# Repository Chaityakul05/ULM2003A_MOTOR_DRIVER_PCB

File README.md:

## ULN2003A Test with ESP and Stepper Motor

This project demonstrates how to drive a 28BYJ-48 stepper motor using the ULN2003A Darlington transistor array with an ESP32 or ESP8266. The ULN2003A is used as a current amplifier and switch to control the stepper motor, which requires more current than the ESP GPIO pins can provide directly. The setup connects the ESP to the four input pins (IN1–IN4) of the ULN2003A, which in turn controls the stepper motor connected to the output pins (OUT1–OUT4). This project helps in understanding how to interface stepper motors with microcontrollers through a driver IC and provides basic motion control using the Arduino Stepper library.

---

##  Example Code (Arduino IDE)

```cpp
#include <Stepper.h>

const int stepsPerRevolution = 2048; // Number of steps per full revolution

// ULN2003 Motor Driver Pins
#define IN1 19
#define IN2 18
#define IN3 5
#define IN4 17

// Initialize the stepper library
Stepper myStepper(stepsPerRevolution, IN1, IN3, IN2, IN4);

void setup() {
  // Set the motor speed in RPM
  myStepper.setSpeed(5);
  
  // Start serial communication
  Serial.begin(115200);
}

void loop() {
  // Step one revolution clockwise
  Serial.println("clockwise");
  myStepper.step(stepsPerRevolution);
  delay(1000);

  // Step one revolution counterclockwise
  Serial.println("counterclockwise");
  myStepper.step(-stepsPerRevolution);
  delay(1000);
}

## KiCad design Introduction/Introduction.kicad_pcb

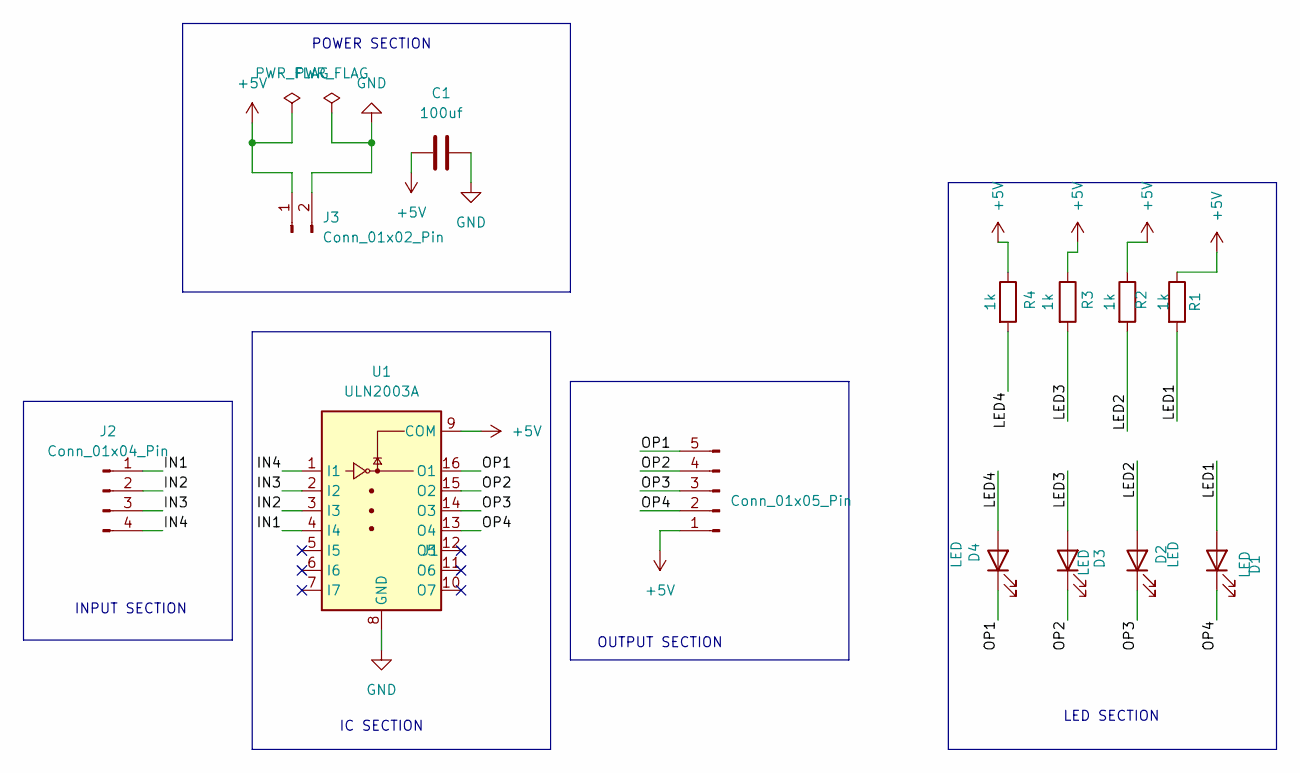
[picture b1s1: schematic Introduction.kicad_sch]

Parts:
C1: 100uf; C_Disc_D3.0mm_W1.6mm_P2.50mm
D1, D2, D3, D4: LED; LED_D5.0mm
J1: Conn_01x05_Pin; JST_EH_B5B-EH-A_1x05_P2.50mm_Vertical
J2: Conn_01x04_Pin; PinHeader_1x04_P2.54mm_Vertical
J3: Conn_01x02_Pin; PinHeader_1x02_P2.54mm_Vertical
R1, R2, R3, R4: 1k; R_Axial_DIN0207_L6.3mm_D2.5mm_P10.16mm_Horizontal
U1: ULN2003A; DIP-16_W7.62mm

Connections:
+5V: C1.1, J1.1, J3.1, R1.1, R2.1, R3.1, R4.1, U1.9 (COM)
/IN1: J2.1, U1.4 (I4)
/IN2: J2.2, U1.3 (I3)
/IN3: J2.3, U1.2 (I2)
/IN4: J2.4, U1.1 (I1)
/LED1: D1.2 (A), R1.2
/LED2: D2.2 (A), R2.2
/LED3: D3.2 (A), R3.2
/LED4: D4.2 (A), R4.2
/OP1: D4.1 (K), J1.5, U1.16 (O1)
/OP2: D3.1 (K), J1.4, U1.15 (O2)
/OP3: D2.1 (K), J1.3, U1.14 (O3)
/OP4: D1.1 (K), J1.2, U1.13 (O4)
GND: C1.2, J3.2, U1.8 (GND)

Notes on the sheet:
INPUT SECTION
OUTPUT SECTION
POWER SECTION
LED SECTION
IC SECTION

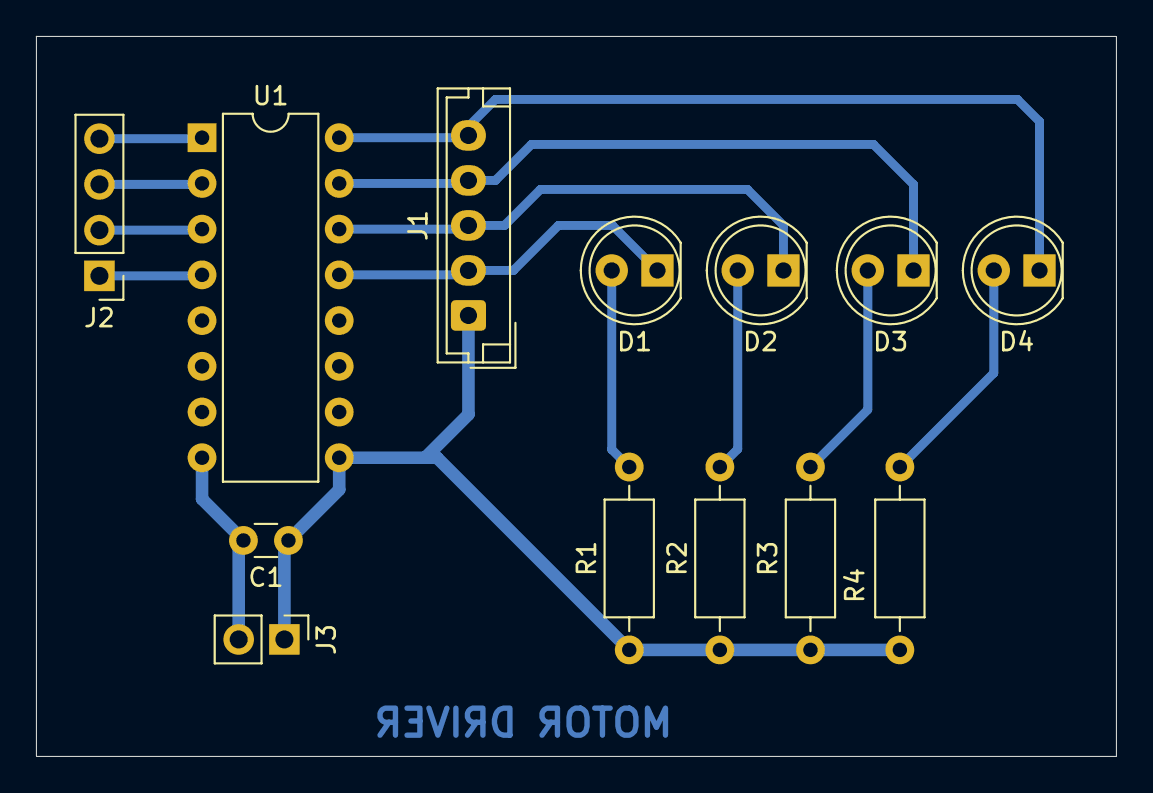
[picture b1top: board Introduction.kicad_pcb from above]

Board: 2 copper layers, 60.0 x 40.0 mm, 13 parts (0 on the bottom side), 14 nets.

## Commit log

2025-04-18 FINAL COMMIT
